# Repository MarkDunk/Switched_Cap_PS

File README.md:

USB powered split rail power supplies. Both use a switched-capacitor topology. The 5V design is based on the LM27762 IC, while the 12V uses discrete components.

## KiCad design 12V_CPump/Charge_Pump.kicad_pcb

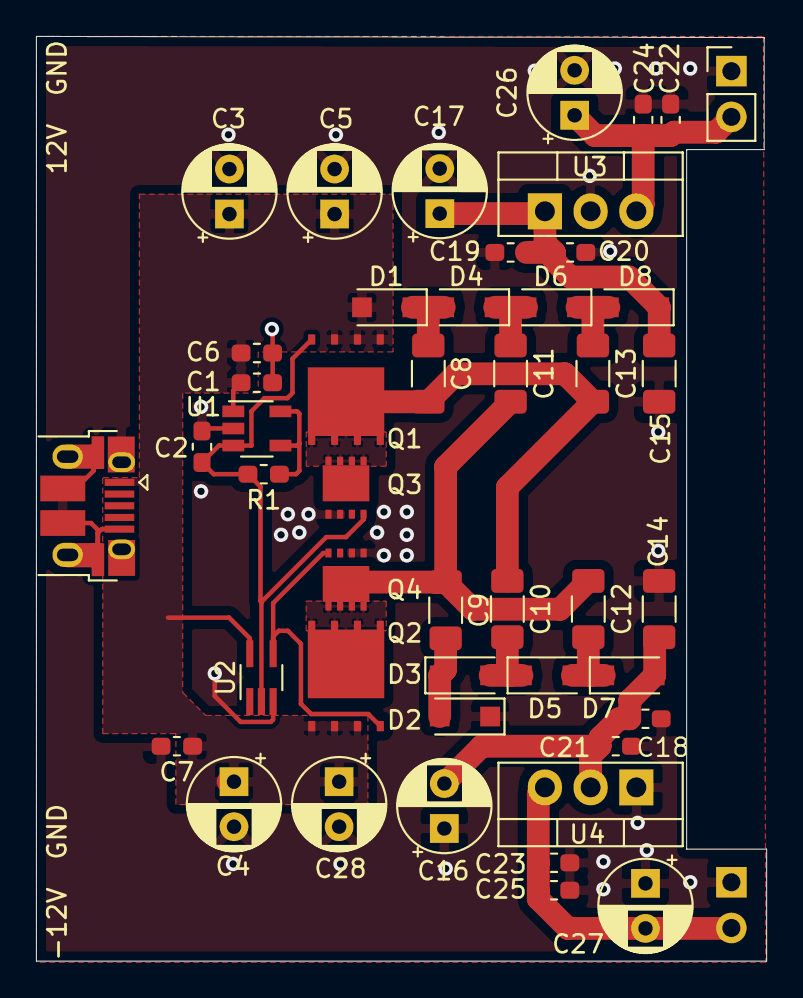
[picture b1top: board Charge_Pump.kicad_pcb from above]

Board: 2 copper layers, 40.6 x 51.4 mm, 48 parts (0 on the bottom side), 17 nets.

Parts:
C1: 10nF; C_0603_1608Metric_Pad1.05x0.95mm_HandSolder
C2: 220pF; C_0603_1608Metric_Pad1.05x0.95mm_HandSolder
C3, C4, C5, C16, C17, C26, C27, C28: CP1; CP_Radial_D5.0mm_P2.50mm
C6, C7, C18, C19, C24, C25: C; C_0603_1608Metric_Pad1.05x0.95mm_HandSolder
C8, C9, C10, C11, C12, C13, C14, C15: C; C_1206_3216Metric_Pad1.33x1.80mm_HandSolder
C20: .33uF; C_0603_1608Metric_Pad1.05x0.95mm_HandSolder
C21: 2.2uF; C_0603_1608Metric_Pad1.05x0.95mm_HandSolder
C22: .1uF; C_0603_1608Metric_Pad1.05x0.95mm_HandSolder
C23: 1uF; C_0603_1608Metric_Pad1.05x0.95mm_HandSolder
D1, D2, D3, D4, D5, D6, D7, D8: PSBD1DF40V2L; D_SOD-123F
J1: USB_B_Micro; USB_Micro-B_Amphenol_10103594-0001LF_Horizontal
J2, J3: Conn_01x02_Male; PinHeader_1x02_P2.54mm_Vertical
Q1, Q2: HY12P03C2; PPAK5-8L
Q3, Q4: ET6300; PDFN3333
R1: 1K; R_0603_1608Metric_Pad1.05x0.95mm_HandSolder
U1: MIC1555; TSOT-23-5
U2: NL17SZU04DFT2G; SOT-353_SC-70-5_Handsoldering
U3: L7812; TO-220-3_Vertical
U4: L7912; TO-220-3_Vertical

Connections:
/5V: C1.1, C3.1, C4.1, C5.1, C6.1, C7.1, C28.1, D1.2, J1.1, Q1.1, Q1.2, Q1.3, Q2.1, Q2.2, Q2.3, U1.1, U2.5
/12V: C22.1, C24.1, C26.1, J2.2, U3.3
/-12V: C23.2, C25.2, C27.2, J3.2, U4.3
/B1: C8.2, C10.1, C13.2, Q1.5, Q3.5
/B2: C9.1, C11.2, C12.1, Q2.5, Q4.5
/CLK: C2.2, Q1.4, Q3.4, R1.2, U1.3, U2.2
/CP_OUT: C15.1, C17.1, C19.1, C20.1, D8.1, U3.1
/NCLK: Q2.4, Q4.4, U2.4
/NCP_OUT: C14.2, C16.2, C18.2, C21.2, D7.2, U4.2
/NS1: C9.2, D2.2, D3.1
/NS2: C10.2, D3.2, D5.1
/NS3: C12.2, D5.2, D7.1
/S1: C8.1, D1.1, D4.2
/S2: C11.1, D4.1, D6.2
/S3: C13.1, D6.1, D8.2
GND: C1.2, C2.1, C3.2, C4.2, C5.2, C6.2, C7.2, C14.1, C15.2, C16.1, C17.2, C18.1, C19.2, C20.2, C21.1, C22.2, C23.1, C24.2, C25.1, C26.2, C27.1, C28.2, D2.1, J1.5, J1.6, J2.1, J3.1, Q3.1, Q3.2, Q3.3, Q4.1, Q4.2, Q4.3, U1.2, U2.3, U3.2, U4.1
unnamed: R1.1, U1.4, U1.5

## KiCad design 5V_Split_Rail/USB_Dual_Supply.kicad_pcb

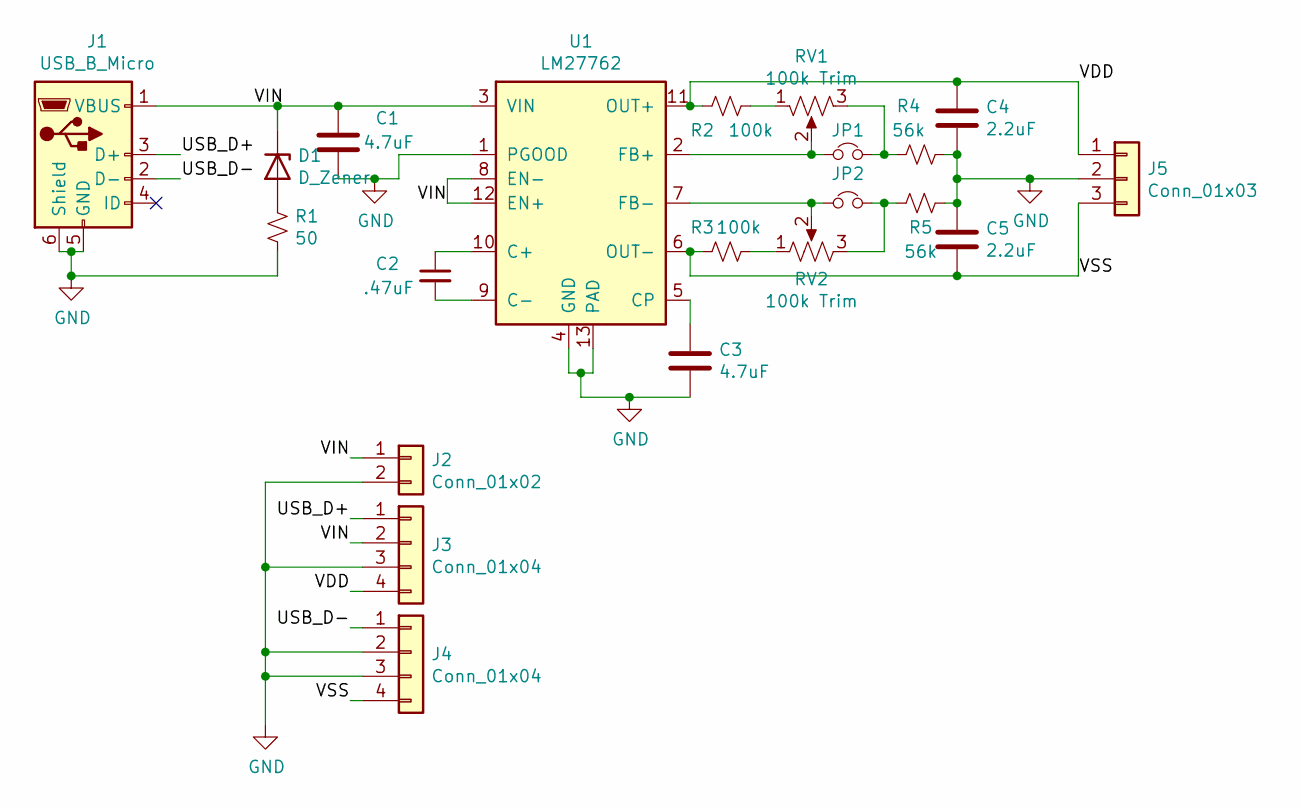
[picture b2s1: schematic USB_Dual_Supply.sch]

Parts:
C1, C3: 4.7uF; C_0603_1608Metric_Pad1.05x0.95mm_HandSolder
C2: .47uF; C_0603_1608Metric_Pad1.05x0.95mm_HandSolder
C4, C5: 2.2uF; C_0603_1608Metric_Pad1.05x0.95mm_HandSolder
D1: D_Zener; D_SOD-123
J1: USB_B_Micro; USB_Micro-B_Amphenol_10103594-0001LF_Horizontal
J2: Conn_01x02; PinHeader_1x02_P2.54mm_Vertical
J3, J4: Conn_01x04; PinHeader_1x04_P2.54mm_Vertical
J5: Conn_01x03; PinHeader_1x03_P2.54mm_Vertical
JP1, JP2: Jumper_NC_Small; SolderJumper-2_P1.3mm_Bridged_RoundedPad1.0x1.5mm
R1: 50; R_0603_1608Metric_Pad0.98x0.95mm_HandSolder
R2, R3: 100k; R_0603_1608Metric_Pad0.98x0.95mm_HandSolder
R4, R5: 56k; R_0603_1608Metric_Pad0.98x0.95mm_HandSolder
RV1, RV2: 100k Trim; Potentiometer_Bourns_TC33X_Vertical
U1: LM27762; WSON-12-1EP_3x2mm_P0.5mm_EP1x2.65_ThermalVias

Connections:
/USB_D+: J1.3 (D+), J3.1
/USB_D-: J1.2 (D-), J4.1
/VDD: C4.1, J3.4, J5.1, R2.2, U1.11 (OUT+)
/VIN: C1.1, D1.1 (K), J1.1 (VBUS), J2.1, J3.2, U1.3 (VIN), U1.8 (EN-), U1.12 (EN+)
/VSS: C5.2, J4.4, J5.3, R3.2, U1.6 (OUT-)
GND: C1.2, C3.2, C4.2, C5.1, J1.5 (GND), J1.6 (Shield), J2.2, J3.3, J4.2, J4.3, J5.2, R1.2, R4.2, R5.2, U1.1 (PGOOD), U1.4 (GND), U1.13 (PAD)
unnamed: C2.1, U1.10 (C+)
unnamed: C2.2, U1.9 (C-)
unnamed: C3.1, U1.5 (CP)
unnamed: D1.2 (A), R1.1
unnamed: JP1.1, RV1.2, U1.2 (FB+)
unnamed: JP1.2, R4.1, RV1.3
unnamed: JP2.1, RV2.2, U1.7 (FB-)
unnamed: JP2.2, R5.1, RV2.3
unnamed: R2.1, RV1.1
unnamed: R3.1, RV2.1

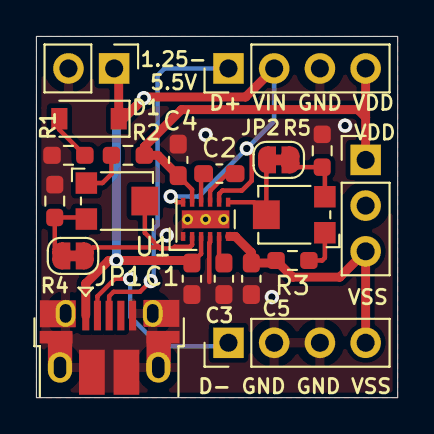
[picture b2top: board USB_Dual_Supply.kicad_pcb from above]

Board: 2 copper layers, 20.1 x 20.1 mm, 21 parts (0 on the bottom side), 16 nets.

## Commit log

2022-01-10 Commit of designs
    Split rail power supplies for 5 and 12V from a usb source.
